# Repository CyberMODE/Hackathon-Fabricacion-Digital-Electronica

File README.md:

# Hackathón de fabricación dixital de deseño e produción de circuítos electrónicos

Neste hackathón aprenderedemos a deseñar as nosas PCB co software libre KiCad, partindo do esquema ao deseño do ciruito para compoñentes THD e SMD.

Unha vez que temos o PCB deseñado, veremos como xerar os ficheiros para crear as nosas placas, os ficheiros Gerbers para enviar a fabricar, ou SVG para fabricar en local cunha CNC.

Usando Gimp xeraremos os PNG necesarios para fresarlo na PCB, ou os negativos para facer a PCB con outros medios.

O exercicio que faremos é unha pequena PCB para aloxar un microcontrolador ATtiny412 que acenda e apague un LED.

Unha vez teñamos a PCB fresada, aprenderemos a soldar compoñentes SMD, usando nosas PCB e os compoñentes que serán proporcionados a cada participante do Hackathon.

Unha vez soldada a placa e revisada que este todo correctamente pasaremos a programar o microcontrolador mediante Arduino.

Ao final do día cada participante terá a habilidade de crear as súas propias PCB e programar as súas microcontroladores, un punto de partida para facer prototipos funcionais a baixo custo.

# Equipo necesario

Cada alumno debe traer o seu computador PC/Mac/Linux co seguinte software instalado:

- KiCad 6.x https://www.kicad.org
- Gimp http://www.gimp.org.es/descargar-gimp.html
- GSender https://sienci.com/gsender/
- Arduino https://www.arduino.cc/en/software

Proporcionarase en caso de non telo instalado acceso a internet para descargalos e memoría USB´s co instalador do software.

# Recursos online

Fab electronics component library for KiCad https://gitlab.fabcloud.org/pub/libraries/electronics/kicad

Mods Project http://modsproject.org

ATtiny library for Arduino IDE http://drazzy.com/package_drazzy.com_index.json

FTDI Drivers https://ftdichip.com/drivers/vcp-drivers/

# Lista de materiais BOM

- Placas de Circuito de PCB **FR1** [Amazon](https://www.amazon.es/dp/B087M1GDCP?psc=1&smid=A839N7HCQOMKL&ref_=chk_typ_imgToDp)
- Fresa 0.4 End Mill -> 1/32 -> 0,4 MM -> TRACES [Aliexpress](https://es.aliexpress.com/item/32914096470.html?spm=a2g0o.order_list.0.0.19bb194dGODsyC&gatewayAdapt=glo2esp)
- Fresa 0.8 End Mill -> 1/64 -> 0,8 MM -> CUT [Aliexpress](https://es.aliexpress.com/item/32914096470.html?spm=a2g0o.order_list.0.0.19bb194dGODsyC&gatewayAdapt=glo2esp)

| Compoñente | Unidades | Código | Tenda | Footprint |
| ----- | ---- | ---- | ---- | ---- |
| ATtiny412 | 1 | ATTINY412-SSF-ND | [Digikey](https://www.digikey.es/en/products/detail/microchip-technology/ATTINY412-SSF/9947539) | SOIC-8_3.9x4.9mm_P1.27mm |
| Cap 10 uF | 1 | GRT31CC8YA106ME01L | [Digikey](https://www.digikey.es/en/products/detail/murata-electronics/GRT31CC8YA106ME01L/5416847) | C_1206 |
| Res 499 Ohms | 1 | RC1206FR-07499RL | [Digikey](https://www.digikey.es/en/products/detail/yageo/RC1206FR-07499RL/728944) | R_1206 |
| LED RED | 1 | 1516-1076-1-ND  | [Digikey](https://www.digikey.es/es/products/detail/qt-brightek-qtb/QBLP615-R/4814674) | LED_1206 |
| Connector 1x03_P2.54mm_Horizontal | 3 | S1143E-36-ND  | [Digikey](https://www.digikey.es/es/products/detail/sullins-connector-solutions/GBC36SGSN-M89/862355) | PinHeader_1x03_P2.54mm_Horizontal_SMD |

# Soldar SMD

# Otros enlaces

- [Fab Academy](https://fabacademy.org)
- [Amigus Labs](https://www.amiguslabs.org)
- [A Industriosa](https://aindustriosa.org)
- [Mancomun](https://www.mancomun.gal/es/)

#### Evento patrocinado por Xunta de Galicia e Amtega Axencia para a Modernización Tecnolóxica

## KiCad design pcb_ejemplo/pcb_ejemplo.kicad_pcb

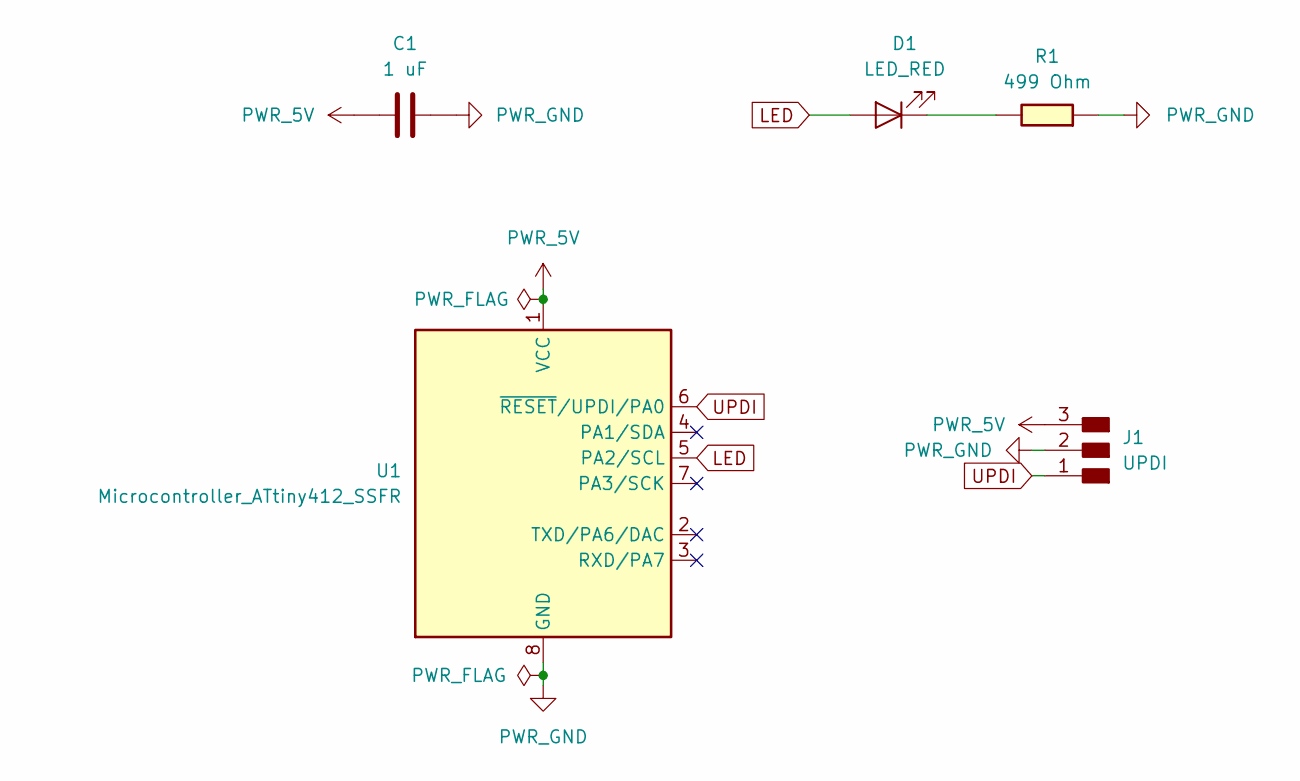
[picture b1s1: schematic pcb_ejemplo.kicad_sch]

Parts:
C1: 1 uF; C_1206
D1: LED_RED; LED_1206
J1: UPDI; PinHeader_1x03_P2.54mm_Horizontal_SMD
R1: 499 Ohm; R_1206
U1: Microcontroller_ATtiny412_SSFR; SOIC-8_3.9x4.9mm_P1.27mm

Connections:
LED: D1.2 (A), U1.5 (PA2/SCL)
unnamed: D1.1 (K), R1.1
PWR_5V: C1.1, J1.3, U1.1 (VCC)
PWR_GND: C1.2, J1.2, R1.2, U1.8 (GND)
UPDI: J1.1, U1.6 (~RESET/UPDI/PA0)

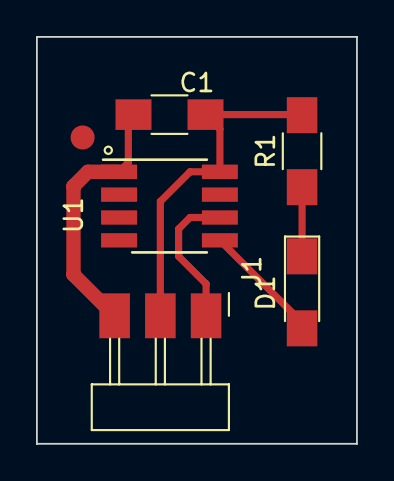
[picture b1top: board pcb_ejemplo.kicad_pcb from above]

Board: 2 copper layers, 17.8 x 22.6 mm, 5 parts (0 on the bottom side), 5 nets.

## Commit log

2022-09-20 nueva imagen
2022-09-20 New files
2022-09-22 TEST CNC
2022-09-26 Diode led test
2022-09-26 diode_led_test
2022-09-30 nuevo
2022-09-30 Arduino
2022-10-03 update PCB
